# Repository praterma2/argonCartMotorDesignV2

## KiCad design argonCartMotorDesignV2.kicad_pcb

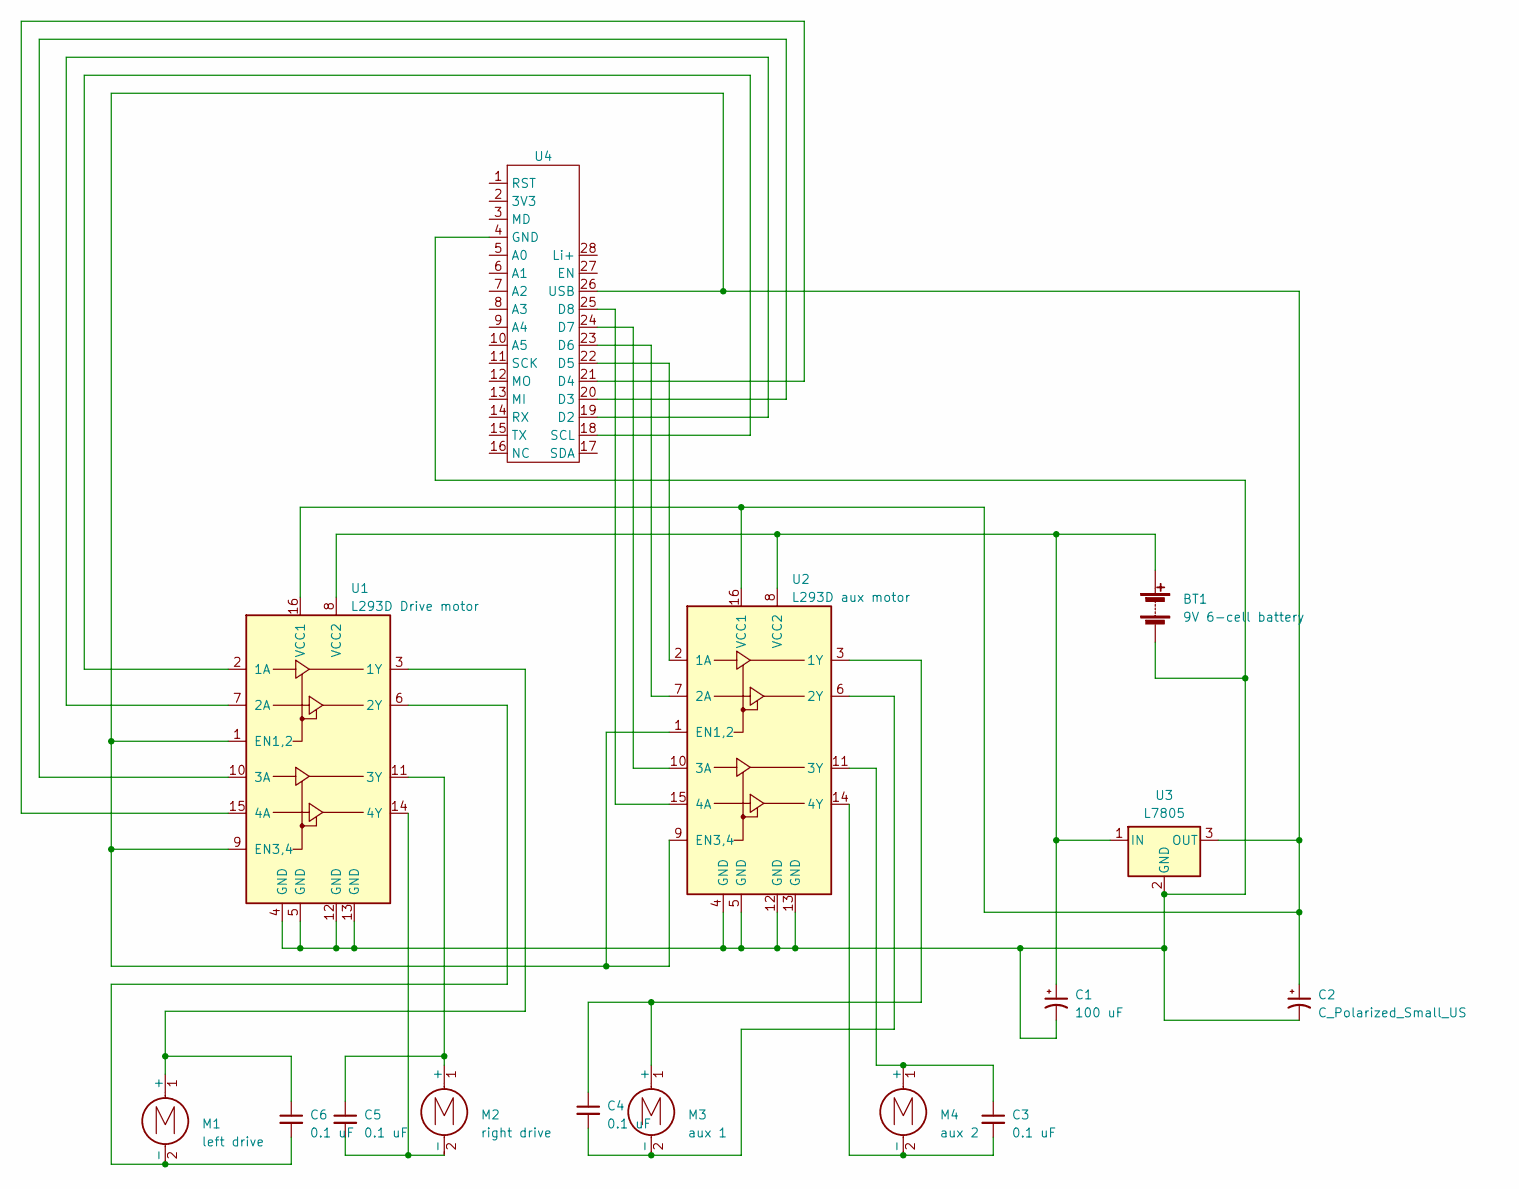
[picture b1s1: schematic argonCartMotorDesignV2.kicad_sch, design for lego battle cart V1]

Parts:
BT1: 9V 6-cell battery; JST_XH_B2B-XH-AM_1x02_P2.50mm_Vertical
C1: 100 uF; C_Radial_D10.0mm_H12.5mm_P5.00mm
C2: C_Polarized_Small_US; C_Radial_D10.0mm_H12.5mm_P5.00mm
C3, C4, C5, C6: 0.1 uF; C_Disc_D3.4mm_W2.1mm_P2.50mm
M1: left drive; JST_XH_B2B-XH-AM_1x02_P2.50mm_Vertical
M2: right drive; JST_XH_B2B-XH-AM_1x02_P2.50mm_Vertical
M3: aux 1; JST_XH_B2B-XH-AM_1x02_P2.50mm_Vertical
M4: aux 2; JST_XH_B2B-XH-AM_1x02_P2.50mm_Vertical
U1: L293D Drive motor; DIP-16_W7.62mm
U2: L293D aux motor; DIP-16_W7.62mm
U3: L7805; TO255P1020X450X2000-3
U4: Argon

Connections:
unnamed: BT1.1 (+), C1.1, U1.8 (VCC2), U2.8 (VCC2), U3.1 (IN)
unnamed: BT1.2 (-), C1.2, C2.2, U1.4 (GND), U1.5 (GND), U1.12 (GND), U1.13 (GND), U2.4 (GND), U2.5 (GND), U2.12 (GND), U2.13 (GND), U3.2 (GND), U4.4 (GND)
unnamed: C6.1, M1.1 (+), U1.3 (1Y)
unnamed: C6.2, M1.2 (-), U1.6 (2Y)
unnamed: C5.1, M2.1 (+), U1.11 (3Y)
unnamed: C5.2, M2.2 (-), U1.14 (4Y)
unnamed: C4.1, M3.1 (+), U2.3 (1Y)
unnamed: C4.2, M3.2 (-), U2.6 (2Y)
unnamed: C3.1, M4.1 (+), U2.11 (3Y)
unnamed: C3.2, M4.2 (-), U2.14 (4Y)
unnamed: U1.2 (1A), U4.18 (SCL)
unnamed: U1.7 (2A), U4.19 (D2)
unnamed: U1.10 (3A), U4.20 (D3)
unnamed: U1.15 (4A), U4.21 (D4)
unnamed: C2.1, U1.1 (EN1,2), U1.9 (EN3,4), U1.16 (VCC1), U2.1 (EN1,2), U2.9 (EN3,4), U2.16 (VCC1), U3.3 (OUT), U4.26 (USB)
unnamed: U2.2 (1A), U4.22 (D5)
unnamed: U2.7 (2A), U4.23 (D6)
unnamed: U2.10 (3A), U4.24 (D7)
unnamed: U2.15 (4A), U4.25 (D8)

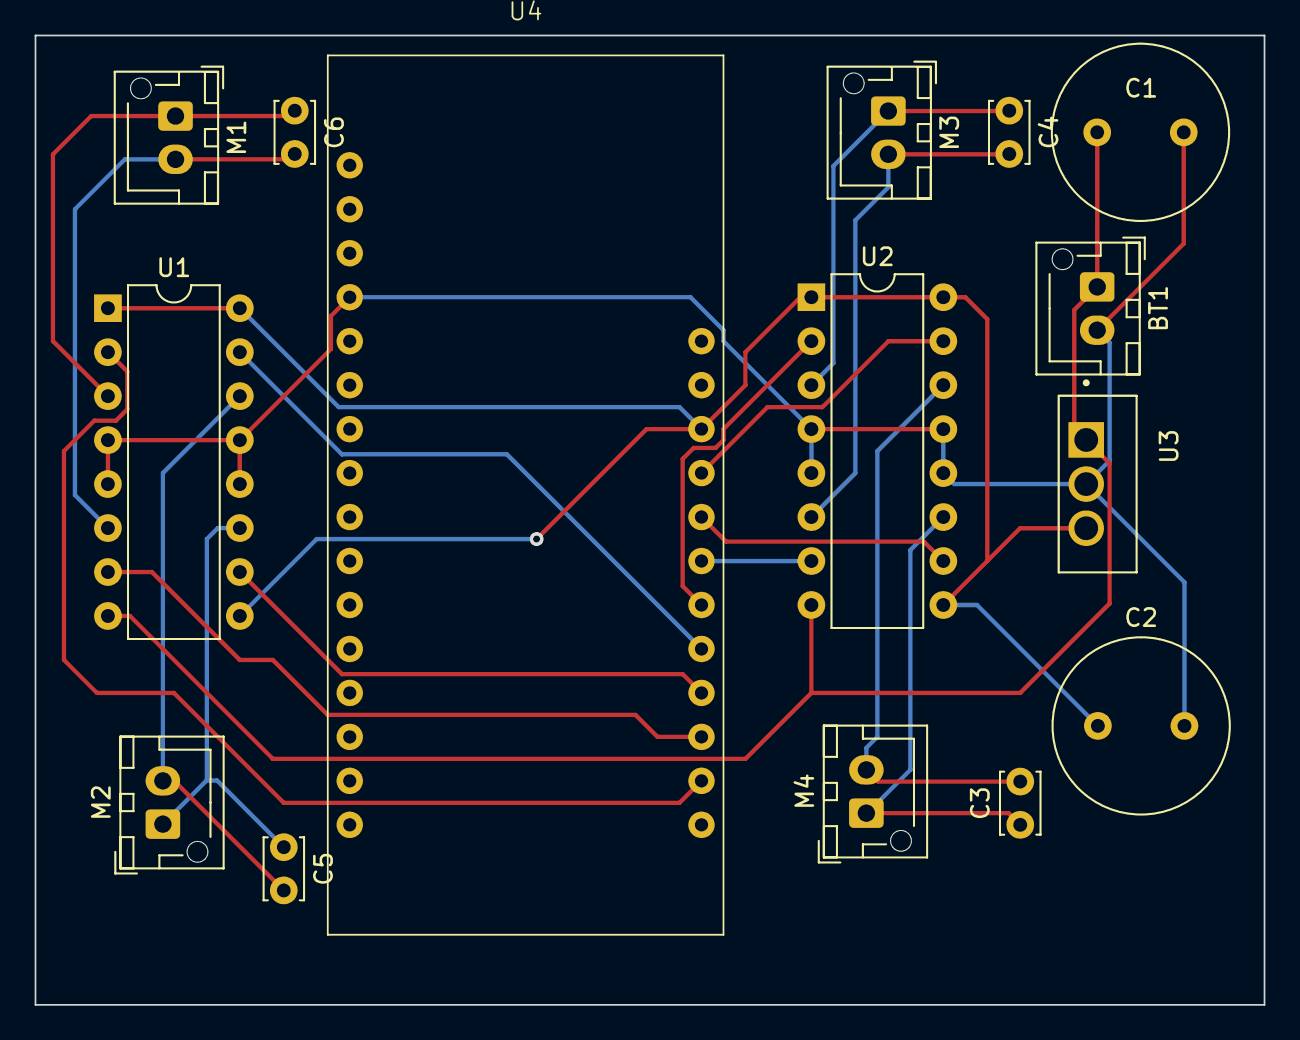
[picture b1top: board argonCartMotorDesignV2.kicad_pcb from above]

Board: 2 copper layers, 71.0 x 56.0 mm, 15 parts (0 on the bottom side), 19 nets.
